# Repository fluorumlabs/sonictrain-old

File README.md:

# FluorumLabs / SonicTrain

This is the schematics and PCB repository for the second revision of SonicTrain: Hardware analog audio signal chain modules.

Version: 0.1-alpha2

Modules

Module | Revision | Status | Current Consumption (+15V / -15V) | Known issues
------ | -------- | ----------- | ------------ | ------- |
M101 Power Supply | B | Tested | | Polarity protection diode bridge is getting hot (50ºC) (#24)
M202 Stereo Input | C | Tested | 21mA / 35mA |
M303 Stereo Output | C | Tested | 31mA / 45mA |
M907 VU Meter | A | | |
M913 Dev Adapter | A | Tested | 5mA / 5mA | Blue LED is brighter then Red LED (#25)
A111 Fader | A | | |
A210 4-Band EQ | A | | |
A212 Kill EQ | A | | |
A405 Diode Distortion | A | Tested | 55mA / 60mA | Diodes should be connected to ground instead of OpAmp (#19), Output gain too low (#20)
A406 4069 Overdrive | A | | |
D104 LoFi Delay | A | Tested | |
D108 SpinSemi FX | A | Fail |  |
D709 VS1053 Synth | A | | |

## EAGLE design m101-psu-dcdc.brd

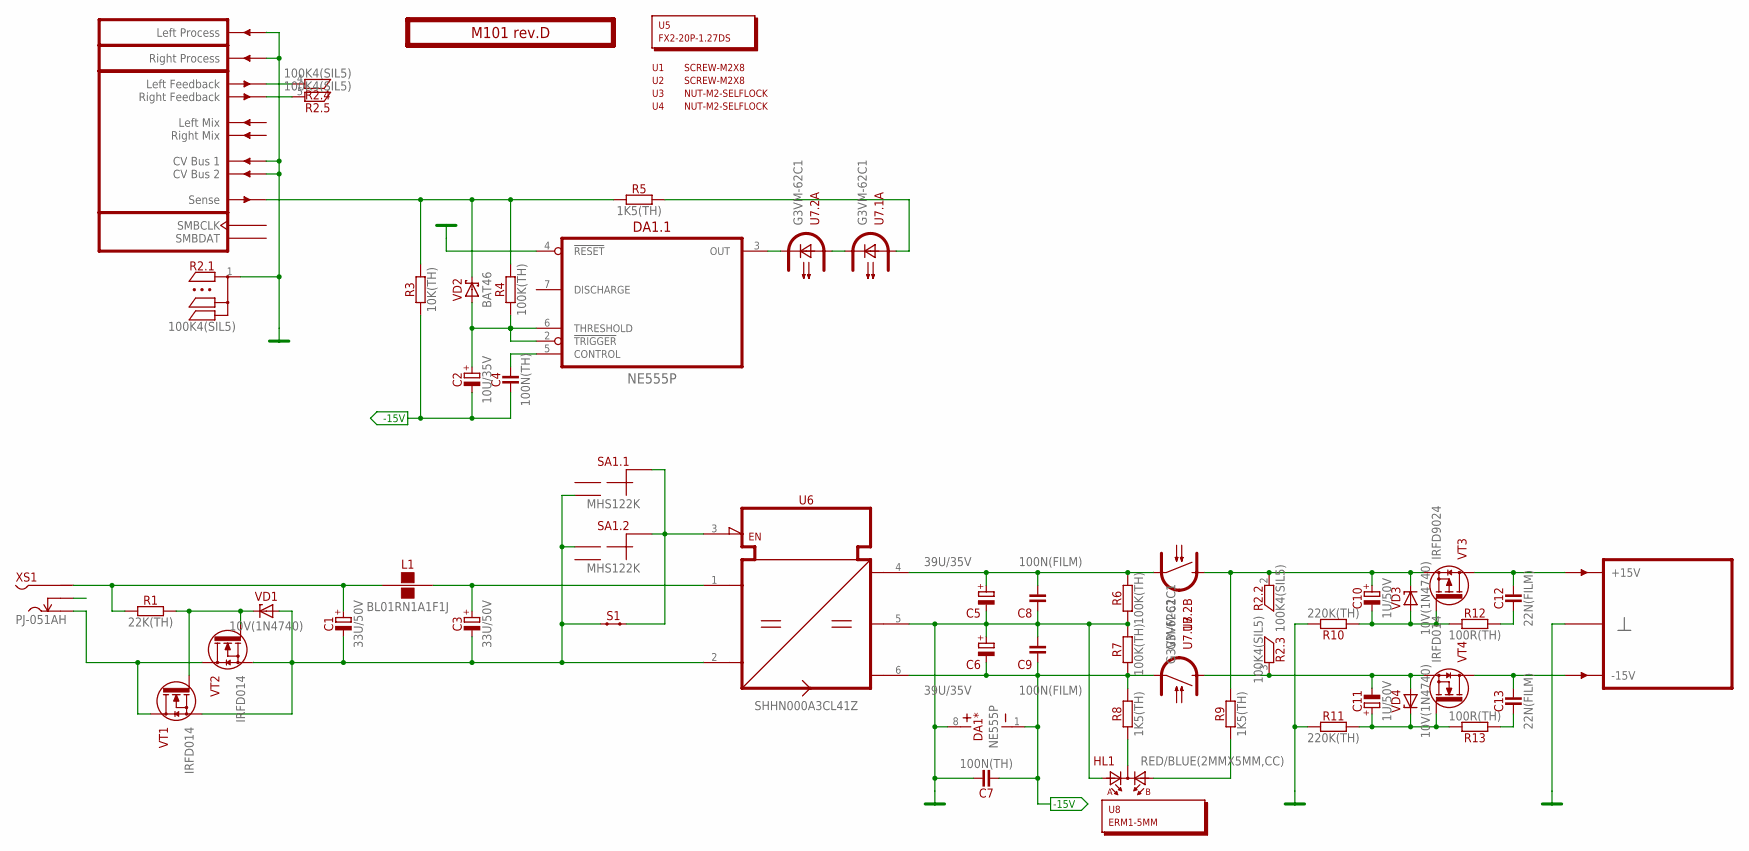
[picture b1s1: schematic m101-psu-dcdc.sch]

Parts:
C1, C3: 33U/50V; E3,5-8
C2: 10U/35V; E2-5
C4, C7: 100N(TH); C050-024X044
C5, C6: 39U/35V; E3,5-8
C8, C9: 100N(FILM); C050-025X075
C10, C11: 1U/50V; E1,5-4
C12, C13: 22N(FILM); C050-025X075
DA1: NE555P; DIP-8
HL1: RED/BLUE(2MMX5MM,CC); LED2X5-3PIN
L1: BL01RN1A1F1J; BL01RN1A
PCB1: M101 rev.D; ST2-BOARD-50-PSU
R1: 22K(TH); R-0207/10
R2: 100K4(SIL5); R-SIL5
R3: 10K(TH); R-0207/10
R4, R6, R7: 100K(TH); R-0207/10
R5, R8, R9: 1K5(TH); R-0207/10
R10, R11: 220K(TH); R-0207/10
R12, R13: 100R(TH); R-0207/10
S1: JUMPER-1POS-SOLDER; JP1-SOLDER
SA1: MHS122K; APEM-MHS122K
U1, U2: SCREW-M2X8; EMPTY
U3, U4: NUT-M2-SELFLOCK; EMPTY
U5: FX2-20P-1.27DS; EMPTY
U6: SHHN000A3CL41Z; DC/DC-C1
U7: G3VM-62C1; DIL08
U8: ERM1-5MM; EMPTY
VD1, VD3, VD4: 10V(1N4740); DO41-10
VD2: BAT46; DO35-7
VT1, VT2, VT4: IRFD014; HVMDIP-4
VT3: IRFD9024; HVMDIP-4
XS1: PJ-051AH

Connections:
-15V: C2.-, C4.1, C6.-, C7.1, C9.1, DA1.1 (V-), R3.1, R7.1, R8.2, U6.6 (V-), U7.7 (S2)
GND: C5.-, C6.+, C7.2, C8.1, C9.2, DA1.4 (!RESET), DA1.8 (V+), HL1.A1, PCB1.ACV1' (CV1'), PCB1.ACV2' (CV2'), PCB1.B4' (GND), PCB1.B5' (GND), PCB1.B6' (GND), PCB1.B7' (GND), PCB1.B8' (GND), PCB1.BOUTL' (OUTL), PCB1.BOUTR' (OUTR), R2.1, R6.1, R7.2, R10.2, R11.2, U6.5 (GND)
unnamed: R5.2, U7.1 (A)
unnamed: C1.-, C3.-, S1.1, SA1.1' (1), SA1.2, U6.2 (IN-), VD1.A, VT1.4 (S), VT2.4 (S)
unnamed: PCB1.ALFBK' (LFBK'), R2.4
unnamed: PCB1.ARFBK' (RFBK'), R2.5
unnamed: C4.2, DA1.5 (CONTROL)
unnamed: DA1.3 (OUT), U7.4 (C)
unnamed: VT1.1 (D), VT1.2 (D), VT2.1 (D), VT2.2 (D), XS1.3 (S)
unnamed: U7.2 (C), U7.3 (A)
unnamed: C2.+, DA1.2 (!TRIGGER), DA1.6 (THRESHOLD), R4.1, VD2.A
unnamed: C10.+, R2.2, R9.2, U7.6 (S1), VD3.C, VT3.4 (S)
unnamed: R1.2, VD1.C, VT1.3 (G), VT2.3 (G)
unnamed: HL1.K, R8.1
unnamed: HL1.A2, R9.1
unnamed: C5.+, C8.2, R6.2, U6.4 (V+), U7.5 (S2)
unnamed: S1.2, SA1.CMN (CM), SA1.CMN' (CM), U6.3 (EN)
unnamed: C10.-, R10.1, R12.1, VD3.A, VT3.3 (G)
unnamed: C12.2, PCB1.A+15' (P+15V), PCB1.B+15' (P+15V), VT3.1 (D), VT3.2 (D)
unnamed: C12.1, R12.2
unnamed: C1.+, L1.1, R1.1, XS1.1
unnamed: C13.1, PCB1.A-15' (P-15V), PCB1.B-15' (P-15V), VT4.1 (D), VT4.2 (D)
unnamed: C3.+, L1.2, U6.1 (IN+)
unnamed: C13.2, R13.2
unnamed: C11.+, R11.1, R13.1, VD4.C, VT4.3 (G)
unnamed: C11.-, R2.3, U7.8 (S1), VD4.A, VT4.4 (S)
SENSE: PCB1.BSENSE' (SENSE'), R3.2, R4.2, R5.1, VD2.C

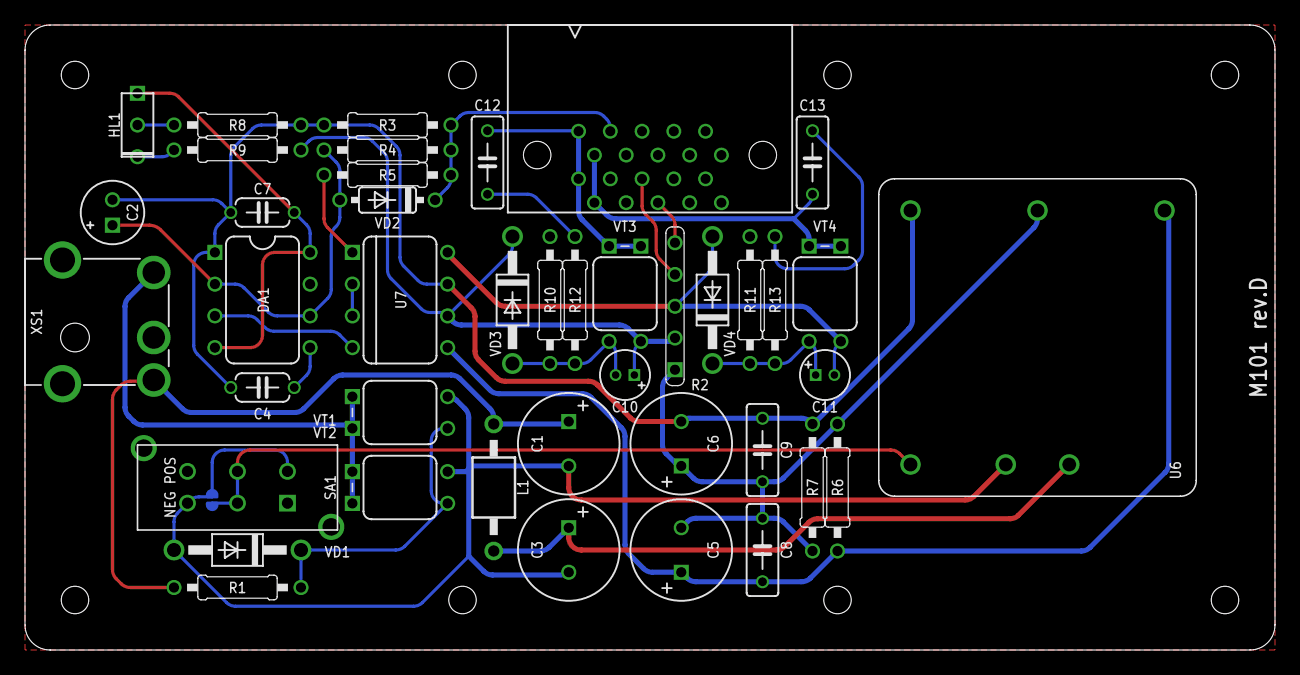
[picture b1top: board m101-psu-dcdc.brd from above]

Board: 2 copper layers, 100.0 x 50.0 mm, 49 parts (1 on the bottom side), 27 nets.

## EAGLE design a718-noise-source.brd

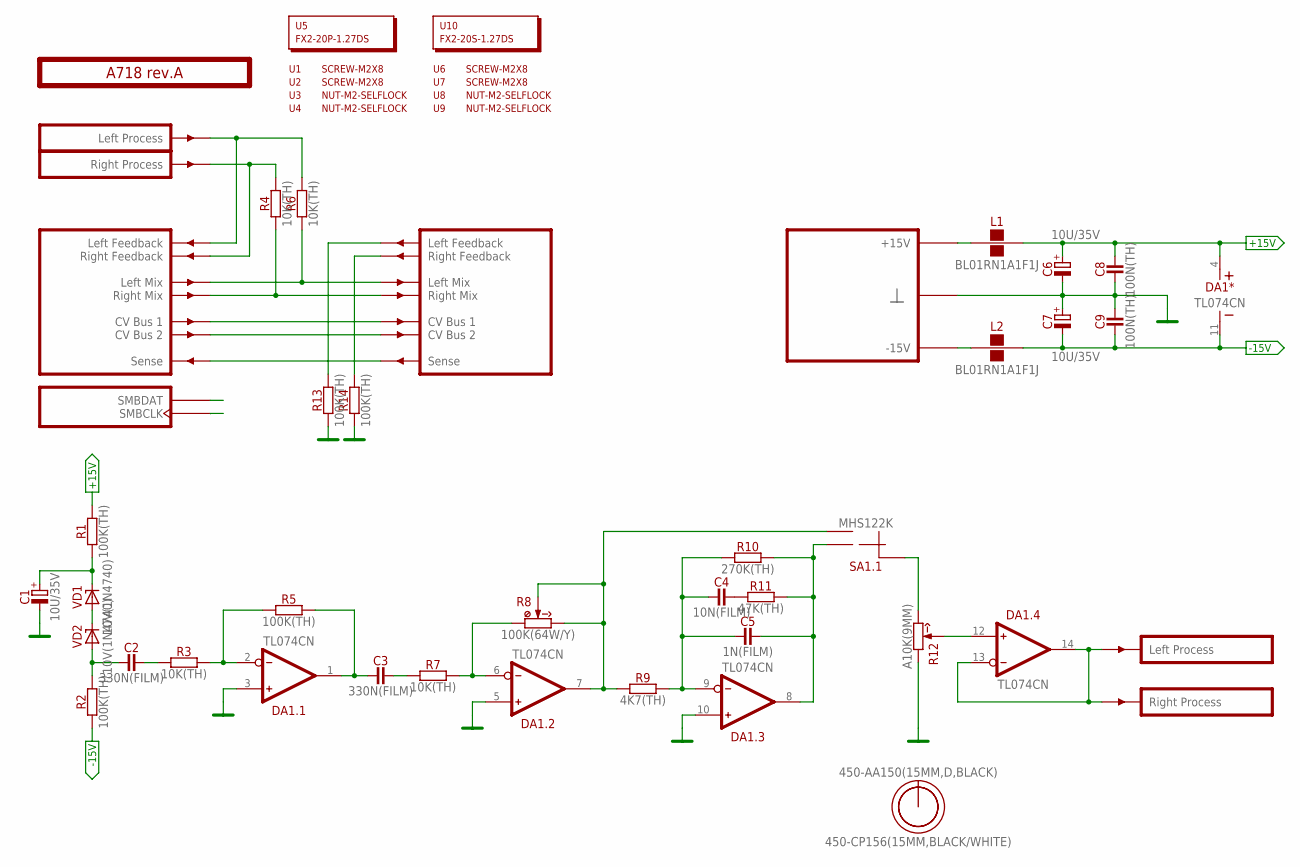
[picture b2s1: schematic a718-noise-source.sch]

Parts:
C1, C6, C7: 10U/35V; E2-5
C2, C3: 330N(FILM); C050-035X075
C4: 10N(FILM); C050-025X075
C5: 1N(FILM); C050-025X075
C8, C9: 100N(TH); C050-024X044
DA1: TL074CN; DIP-14
L1, L2: BL01RN1A1F1J; BL01RN1A
O1: 450-AA150(15MM,D,BLACK); EMPTY
O2: 450-CP156(15MM,BLACK/WHITE); EMPTY
PCB1: A718 rev.A; ST2-BOARD-50
R1, R2, R5, R13, R14: 100K(TH); R-0207/10
R3, R4, R6, R7: 10K(TH); R-0207/10
R8: 100K(64W/Y); 64W
R9: 4K7(TH); R-0207/10
R10: 270K(TH); R-0207/10
R11: 47K(TH); R-0207/10
R12: A10K(9MM); RV09-SINGLE
SA1: MHS122K; APEM-MHS122K
U1, U2, U6, U7: SCREW-M2X8; EMPTY
U3, U4, U8, U9: NUT-M2-SELFLOCK; EMPTY
U5: FX2-20P-1.27DS; EMPTY
U10: FX2-20S-1.27DS; EMPTY
VD1, VD2: 10V(1N4740); DO41-10

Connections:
+15V: C6.+, C8.2, DA1.4 (V+), L1.2, R1.2
-15V: C7.-, C9.1, DA1.11 (V-), L2.2, R2.1
GND: C1.-, C6.-, C7.+, C8.1, C9.2, DA1.3 (IN+), DA1.5 (IN+), DA1.10 (IN+), PCB1.B4 (GND), PCB1.B4' (GND), PCB1.B5 (GND), PCB1.B5' (GND), PCB1.B6 (GND), PCB1.B6' (GND), PCB1.B7 (GND), PCB1.B7' (GND), PCB1.B8 (GND), PCB1.B8' (GND), R12.1 (CCW), R13.1, R14.1
LMIX: PCB1.ALMIX (LMIX), PCB1.ALMIX' (LMIX'), R6.1
unnamed: L1.1, PCB1.A+15 (P+15V), PCB1.A+15' (P+15V), PCB1.B+15 (P+15V), PCB1.B+15' (P+15V)
unnamed: C1.+, R1.1, VD1.C
unnamed: PCB1.ARFBK' (RFBK'), R14.2
unnamed: VD1.A, VD2.C
unnamed: L2.1, PCB1.A-15 (P-15V), PCB1.A-15' (P-15V), PCB1.B-15 (P-15V), PCB1.B-15' (P-15V)
unnamed: PCB1.ALFBK' (LFBK'), R13.2
unnamed: C2.1, R2.2, VD2.A
unnamed: C4.1, C5.1, DA1.9 (IN-), R9.2, R10.1
unnamed: C2.2, R3.1
unnamed: DA1.2 (IN-), R3.2, R5.1
unnamed: C3.1, DA1.1 (OUT), R5.2
unnamed: C3.2, R7.1
unnamed: DA1.6 (IN-), R7.2, R8.1 (CCW)
unnamed: DA1.7 (OUT), R8.3 (CW), R8.S (W), R8.S@1 (W), R9.1, SA1.2
unnamed: C4.2, R11.1
unnamed: PCB1.BSENSE (SENSE), PCB1.BSENSE' (SENSE')
unnamed: PCB1.ARFBK (RFBK), PCB1.BINR (INR), R4.2
unnamed: PCB1.ALFBK (LFBK), PCB1.BINL (INL), R6.2
unnamed: C5.2, DA1.8 (OUT), R10.2, R11.2, SA1.1
unnamed: R12.3 (CW), SA1.CMN (CM)
unnamed: DA1.12 (IN+), R12.2 (W)
unnamed: DA1.13 (IN-), DA1.14 (OUT), PCB1.BOUTL' (OUTL), PCB1.BOUTR' (OUTR)
unnamed: PCB1.ASMBDAT (SMBDAT), PCB1.ASMBDAT' (SMBDAT)
unnamed: PCB1.ACV1 (CV1), PCB1.ACV1' (CV1')
unnamed: PCB1.ACV2 (CV2), PCB1.ACV2' (CV2')
unnamed: PCB1.ASMBCLK (SMBCLK), PCB1.ASMBCLK' (SMBCLK)
RMIX: PCB1.ARMIX (RMIX), PCB1.ARMIX' (RMIX'), R4.1

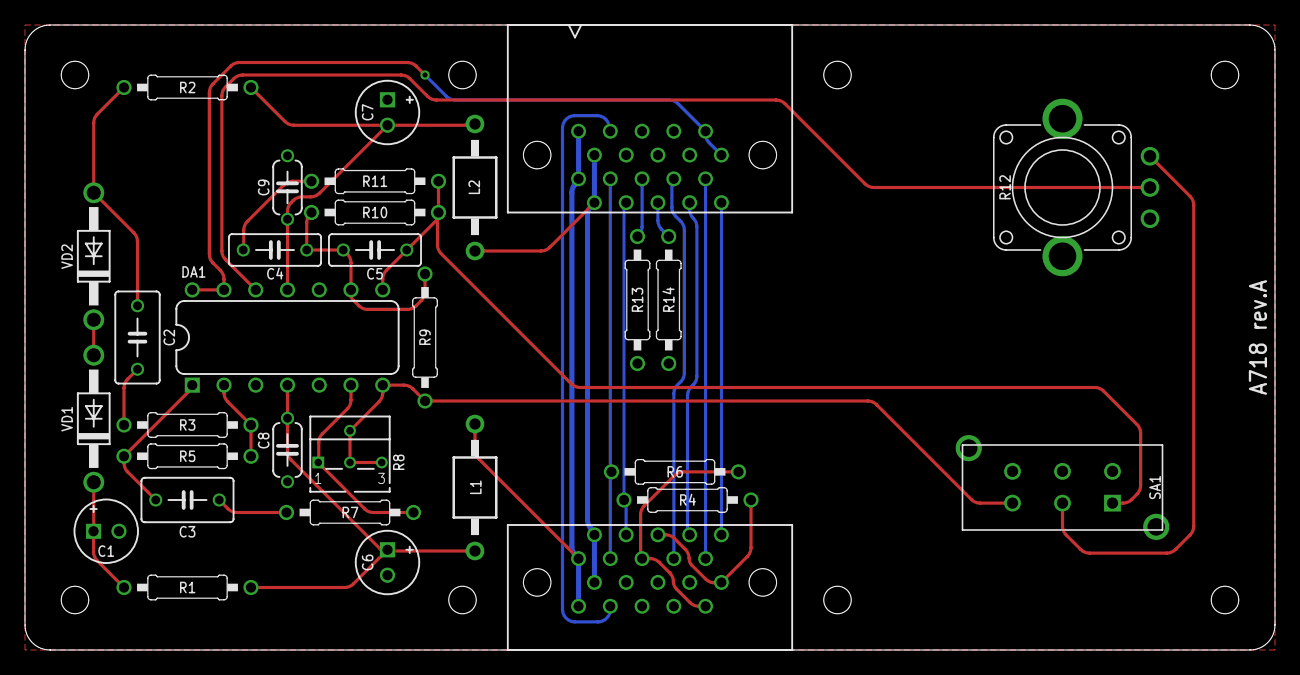
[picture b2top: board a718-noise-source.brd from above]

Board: 2 copper layers, 100.0 x 50.0 mm, 42 parts (0 on the bottom side), 31 nets.

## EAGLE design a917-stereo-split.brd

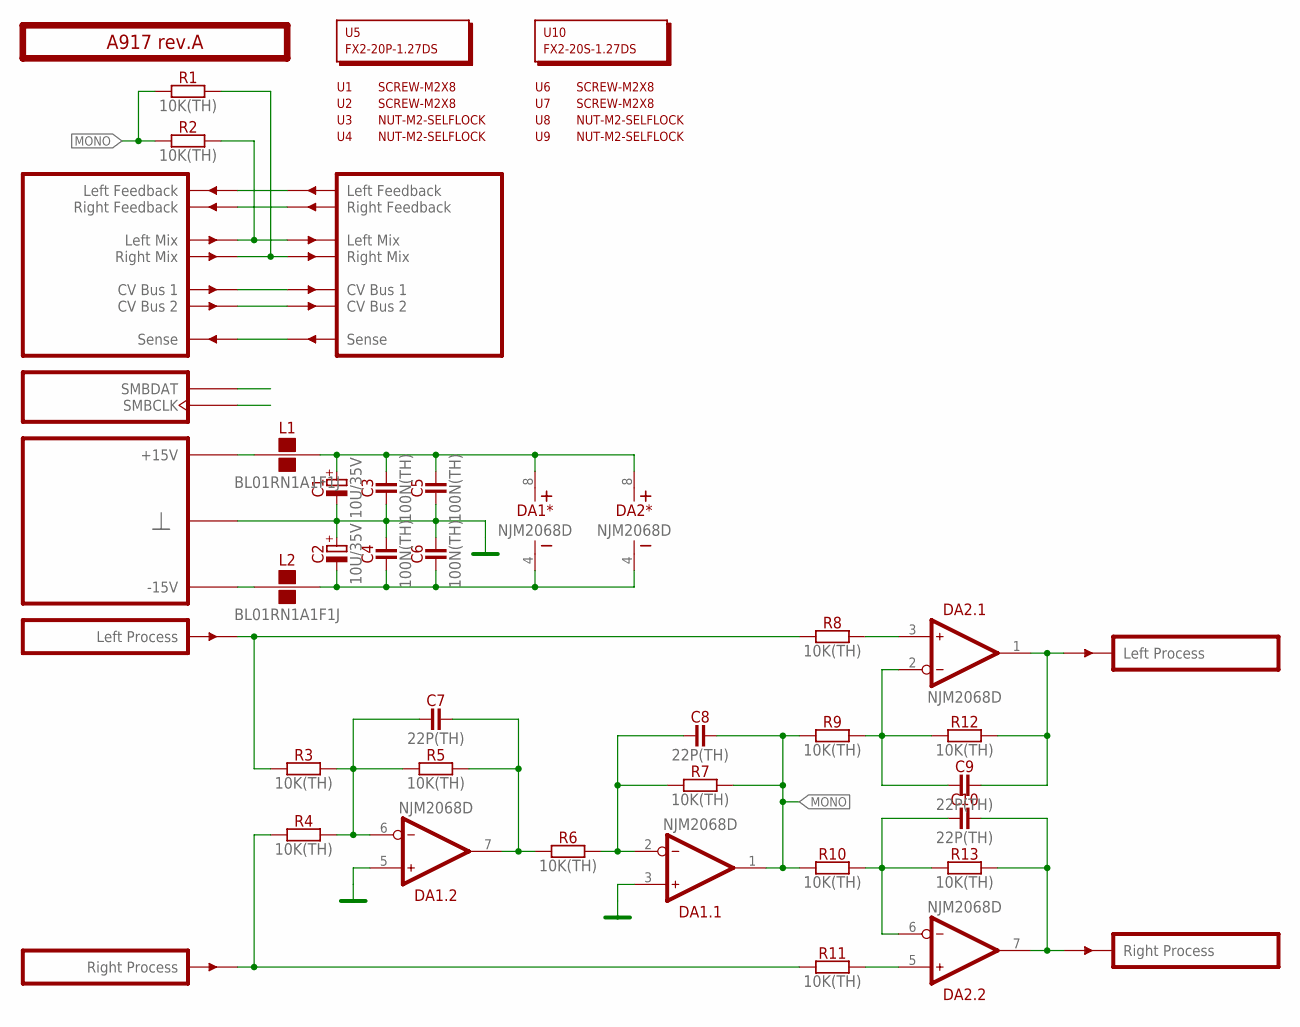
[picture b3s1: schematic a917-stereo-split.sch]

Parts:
C1, C2: 10U/35V; E2-5
C3, C4, C5, C6: 100N(TH); C050-024X044
C7, C8, C9, C10: 22P(TH); C050-024X044
DA1, DA2: NJM2068D; DIP-8
L1, L2: BL01RN1A1F1J; BL01RN1A
PCB1: A917 rev.A; ST2-BOARD-26
R1, R2, R3, R4, R5, R6, R7, R8, R9, R10, R11, R12, R13: 10K(TH); R-0207/10
U1, U2, U6, U7: SCREW-M2X8; EMPTY
U3, U4, U8, U9: NUT-M2-SELFLOCK; EMPTY
U5: FX2-20P-1.27DS; EMPTY
U10: FX2-20S-1.27DS; EMPTY

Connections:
GND: C1.-, C2.+, C3.1, C4.2, C5.1, C6.2, DA1.3 (IN+), DA1.5 (IN+), PCB1.B4 (GND), PCB1.B4' (GND), PCB1.B5 (GND), PCB1.B5' (GND), PCB1.B6 (GND), PCB1.B6' (GND), PCB1.B7 (GND), PCB1.B7' (GND), PCB1.B8 (GND), PCB1.B8' (GND)
MONO: C8.2, DA1.1 (OUT), R1.1, R2.1, R7.2, R9.1, R10.1
unnamed: PCB1.ALFBK (LFBK), PCB1.ALFBK' (LFBK')
unnamed: PCB1.ARFBK (RFBK), PCB1.ARFBK' (RFBK')
unnamed: PCB1.ALMIX (LMIX), PCB1.ALMIX' (LMIX'), R2.2
unnamed: PCB1.ARMIX (RMIX), PCB1.ARMIX' (RMIX'), R1.2
unnamed: PCB1.ACV1 (CV1), PCB1.ACV1' (CV1')
unnamed: PCB1.ACV2 (CV2), PCB1.ACV2' (CV2')
unnamed: PCB1.BSENSE (SENSE), PCB1.BSENSE' (SENSE')
unnamed: PCB1.ASMBDAT (SMBDAT), PCB1.ASMBDAT' (SMBDAT)
unnamed: PCB1.ASMBCLK (SMBCLK), PCB1.ASMBCLK' (SMBCLK)
unnamed: C7.1, DA1.6 (IN-), R3.2, R4.2, R5.1
unnamed: C7.2, DA1.7 (OUT), R5.2, R6.1
unnamed: C8.1, DA1.2 (IN-), R6.2, R7.1
unnamed: DA2.3 (IN+), R8.2
unnamed: C9.1, DA2.2 (IN-), R9.2, R12.1
unnamed: C9.2, DA2.1 (OUT), PCB1.BOUTL' (OUTL), R12.2
unnamed: DA2.5 (IN+), R11.2
unnamed: C10.1, DA2.6 (IN-), R10.2, R13.1
unnamed: C10.2, DA2.7 (OUT), PCB1.BOUTR' (OUTR), R13.2
unnamed: PCB1.BINL (INL), R3.1, R8.1
unnamed: PCB1.BINR (INR), R4.1, R11.1
unnamed: L1.1, PCB1.A+15 (P+15V), PCB1.A+15' (P+15V), PCB1.B+15 (P+15V), PCB1.B+15' (P+15V)
unnamed: C1.+, C3.2, C5.2, DA1.8 (V+), DA2.8 (V+), L1.2
unnamed: L2.1, PCB1.A-15 (P-15V), PCB1.A-15' (P-15V), PCB1.B-15 (P-15V), PCB1.B-15' (P-15V)
unnamed: C2.-, C4.1, C6.1, DA1.4 (V-), DA2.4 (V-), L2.2

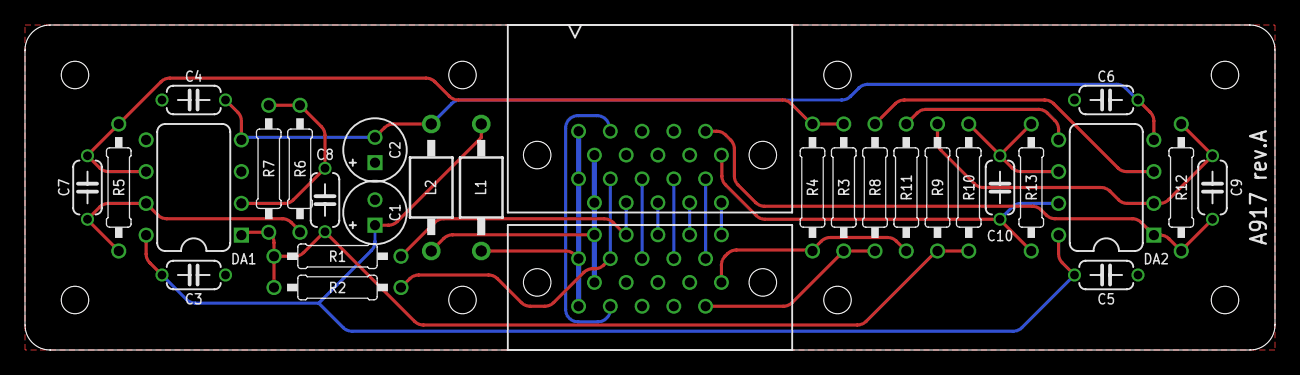
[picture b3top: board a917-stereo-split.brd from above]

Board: 2 copper layers, 100.0 x 26.0 mm, 38 parts (0 on the bottom side), 26 nets.

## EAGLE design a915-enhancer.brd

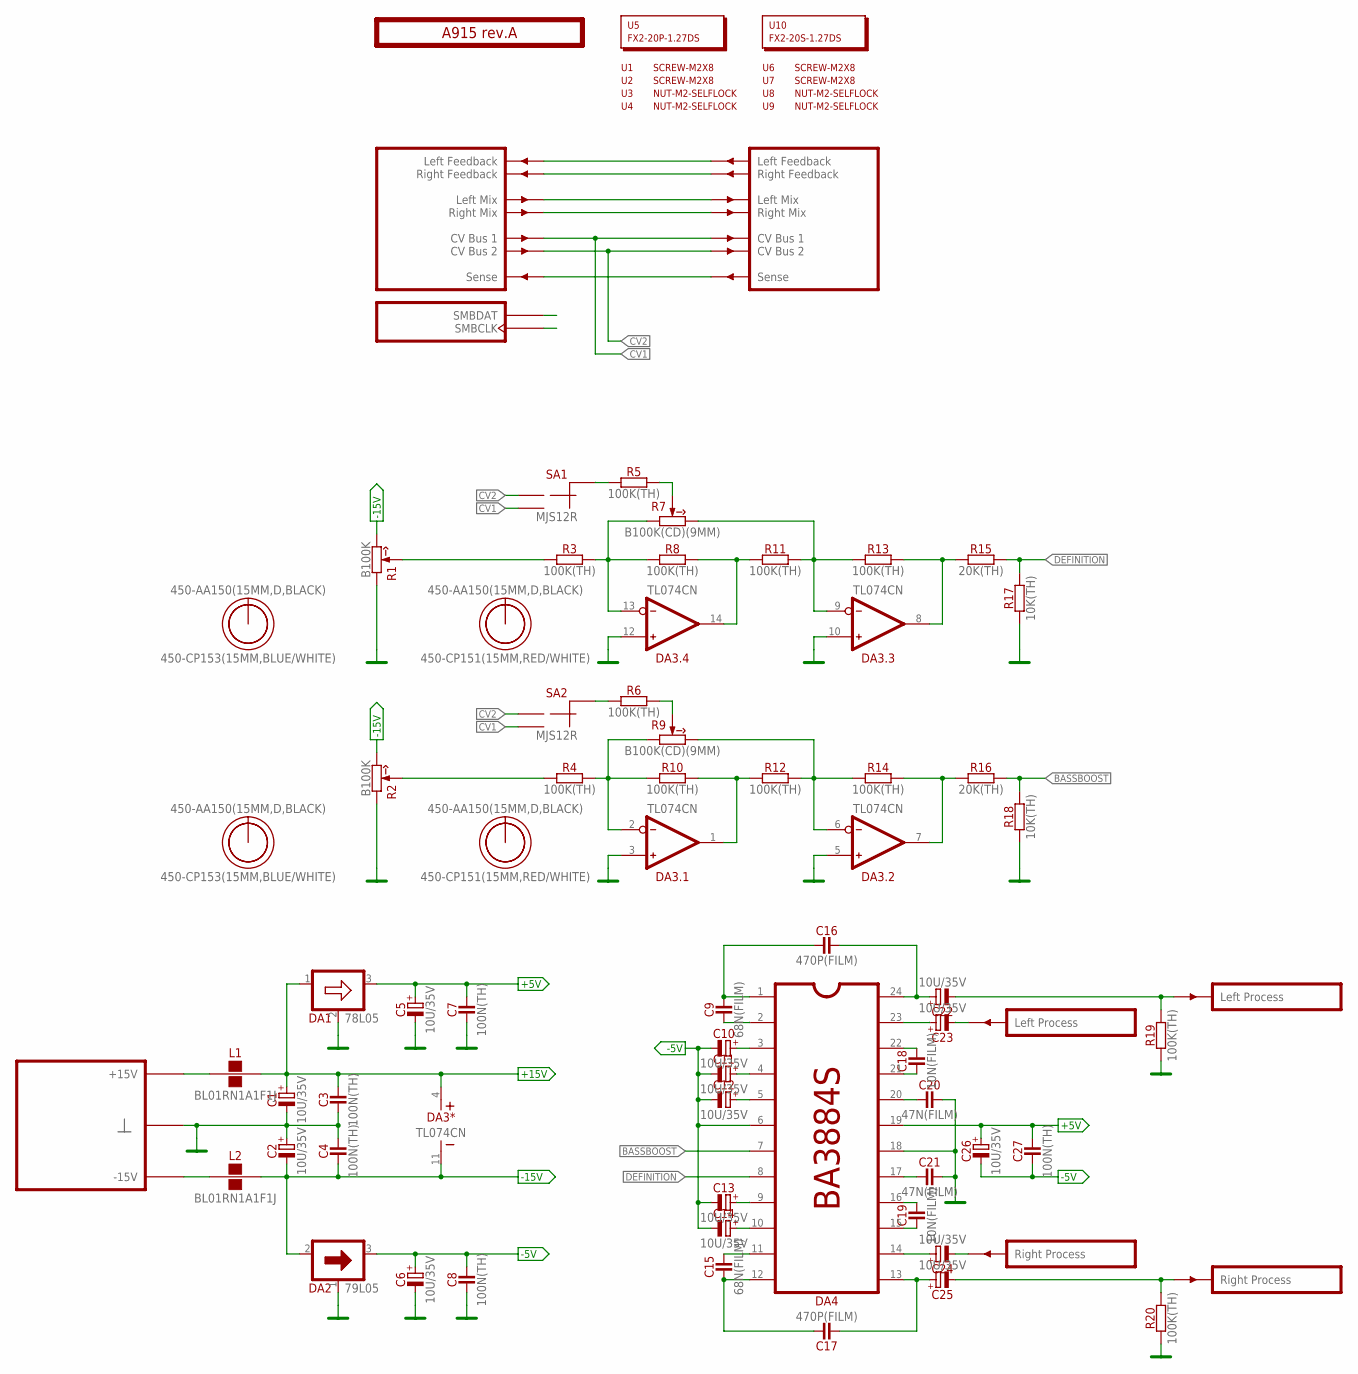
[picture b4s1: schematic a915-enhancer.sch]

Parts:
C1, C2, C5, C6, C10, C11, C12, C13, C14, C22, C23, C24, C25, C26: 10U/35V; E2-5
C3, C4, C7, C8, C27: 100N(TH); C050-024X044
C9, C15: 68N(FILM); C050-025X075
C16, C17: 470P(FILM); C050-055X075
C18, C19: 10N(FILM); C050-025X075
C20, C21: 47N(FILM); C050-025X075
DA1: 78L05; TO92
DA2: 79L05; TO92
DA3: TL074CN; DIP-14
DA4: BA3884S; SDIP-24
L1, L2: BL01RN1A1F1J; BL01RN1A
O1, O3, O5, O7: 450-AA150(15MM,D,BLACK); EMPTY
O2, O4: 450-CP153(15MM,BLUE/WHITE); EMPTY
O6, O8: 450-CP151(15MM,RED/WHITE); EMPTY
PCB1: A915 rev.A; ST2-BOARD-50
R1, R2: B100K; RV11-SINGLE
R3, R4, R5, R6, R8, R10, R11, R12, R13, R14, R19, R20: 100K(TH); R-0207/10
R7, R9: B100K(CD)(9MM); RV09-SINGLE
R15, R16: 20K(TH); R-0207/10
R17, R18: 10K(TH); R-0207/10
SA1, SA2: MJS12R; APEM-MJS12R
U1, U2, U6, U7: SCREW-M2X8; EMPTY
U3, U4, U8, U9: NUT-M2-SELFLOCK; EMPTY
U5: FX2-20P-1.27DS; EMPTY
U10: FX2-20S-1.27DS; EMPTY

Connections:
+5V: C5.+, C7.2, C26.+, C27.2, DA1.3 (OUT), DA4.19
+15V: C1.+, C3.2, DA1.1 (IN), DA3.4 (V+), L1.2
-5V: C6.+, C8.2, C10.-, C11.-, C12.-, C13.-, C14.-, C26.-, C27.1, DA2.3 (OUT), DA4.6
-15V: C2.-, C4.1, DA2.2 (IN), DA3.11 (V-), L2.2, R1.3 (CW), R2.3 (CW)
BASSBOOST: DA4.7, R16.2, R18.2
CV1: PCB1.ACV1 (CV1), PCB1.ACV1' (CV1'), SA1.NO (2), SA2.NO (2)
CV2: PCB1.ACV2 (CV2), PCB1.ACV2' (CV2'), SA1.NC (1), SA2.NC (1)
DEFINITION: DA4.8, R15.2, R17.2
GND: C1.-, C2.+, C3.1, C4.2, C5.-, C6.-, C7.1, C8.1, C20.2, C21.2, DA1.2 (GND), DA2.1 (GND), DA3.3 (IN+), DA3.5 (IN+), DA3.10 (IN+), DA3.12 (IN+), DA4.18, PCB1.B4 (GND), PCB1.B4' (GND), PCB1.B5 (GND), PCB1.B5' (GND), PCB1.B6 (GND), PCB1.B6' (GND), PCB1.B7 (GND), PCB1.B7' (GND), PCB1.B8 (GND), PCB1.B8' (GND), R1.1 (CCW), R2.1 (CCW), R17.1, R18.1, R19.1, R20.1
LMIX: PCB1.ALMIX (LMIX), PCB1.ALMIX' (LMIX')
unnamed: L1.1, PCB1.A+15 (P+15V), PCB1.A+15' (P+15V), PCB1.B+15 (P+15V), PCB1.B+15' (P+15V)
unnamed: PCB1.ALFBK (LFBK), PCB1.ALFBK' (LFBK')
unnamed: R5.2, R7.2 (W)
unnamed: PCB1.ARFBK (RFBK), PCB1.ARFBK' (RFBK')
unnamed: DA3.13 (IN-), R3.2, R7.1 (CCW), R8.1
unnamed: DA3.14 (OUT), R8.2, R11.1
unnamed: DA3.9 (IN-), R7.3 (CW), R11.2, R13.1
unnamed: DA3.8 (OUT), R13.2, R15.1
unnamed: R5.1, SA1.C (CM)
unnamed: R1.2 (W), R3.1
unnamed: C24.+, DA4.14
unnamed: C9.1, DA4.2
unnamed: C9.2, C16.1, DA4.1
unnamed: C15.2, DA4.11
unnamed: C23.+, DA4.23
unnamed: PCB1.BSENSE (SENSE), PCB1.BSENSE' (SENSE')
unnamed: C15.1, C17.2, DA4.12
unnamed: C14.+, DA4.10
unnamed: C13.+, DA4.9
unnamed: C12.+, DA4.5
unnamed: C11.+, DA4.4
unnamed: C10.+, DA4.3
unnamed: C18.1, DA4.21
unnamed: C18.2, DA4.22
unnamed: L2.1, PCB1.A-15 (P-15V), PCB1.A-15' (P-15V), PCB1.B-15 (P-15V), PCB1.B-15' (P-15V)
unnamed: C19.1, DA4.15
unnamed: C19.2, DA4.16
unnamed: C21.1, DA4.17
unnamed: C20.1, DA4.20
unnamed: R6.2, R9.2 (W)
unnamed: DA3.2 (IN-), R4.2, R9.1 (CCW), R10.1
unnamed: C16.2, C22.+, DA4.24
unnamed: C17.1, C25.+, DA4.13
unnamed: DA3.1 (OUT), R10.2, R12.1
unnamed: DA3.6 (IN-), R9.3 (CW), R12.2, R14.1
unnamed: DA3.7 (OUT), R14.2, R16.1
unnamed: R6.1, SA2.C (CM)
unnamed: PCB1.ASMBDAT (SMBDAT), PCB1.ASMBDAT' (SMBDAT)
unnamed: R2.2 (W), R4.1
unnamed: C23.-, PCB1.BINL (INL)
unnamed: C22.-, PCB1.BOUTL' (OUTL), R19.2
unnamed: C24.-, PCB1.BINR (INR)
unnamed: PCB1.ASMBCLK (SMBCLK), PCB1.ASMBCLK' (SMBCLK)
unnamed: C25.-, PCB1.BOUTR' (OUTR), R20.2
RMIX: PCB1.ARMIX (RMIX), PCB1.ARMIX' (RMIX')

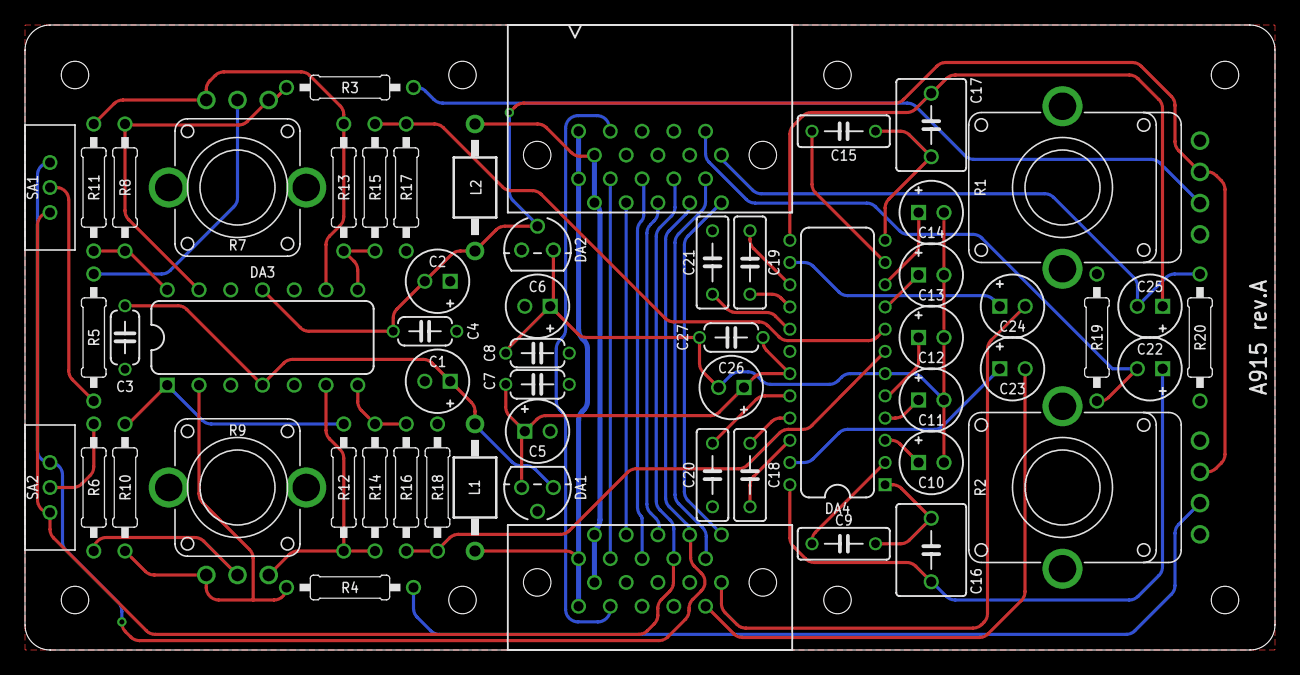
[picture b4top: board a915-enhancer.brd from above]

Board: 2 copper layers, 100.0 x 50.0 mm, 74 parts (0 on the bottom side), 55 nets.

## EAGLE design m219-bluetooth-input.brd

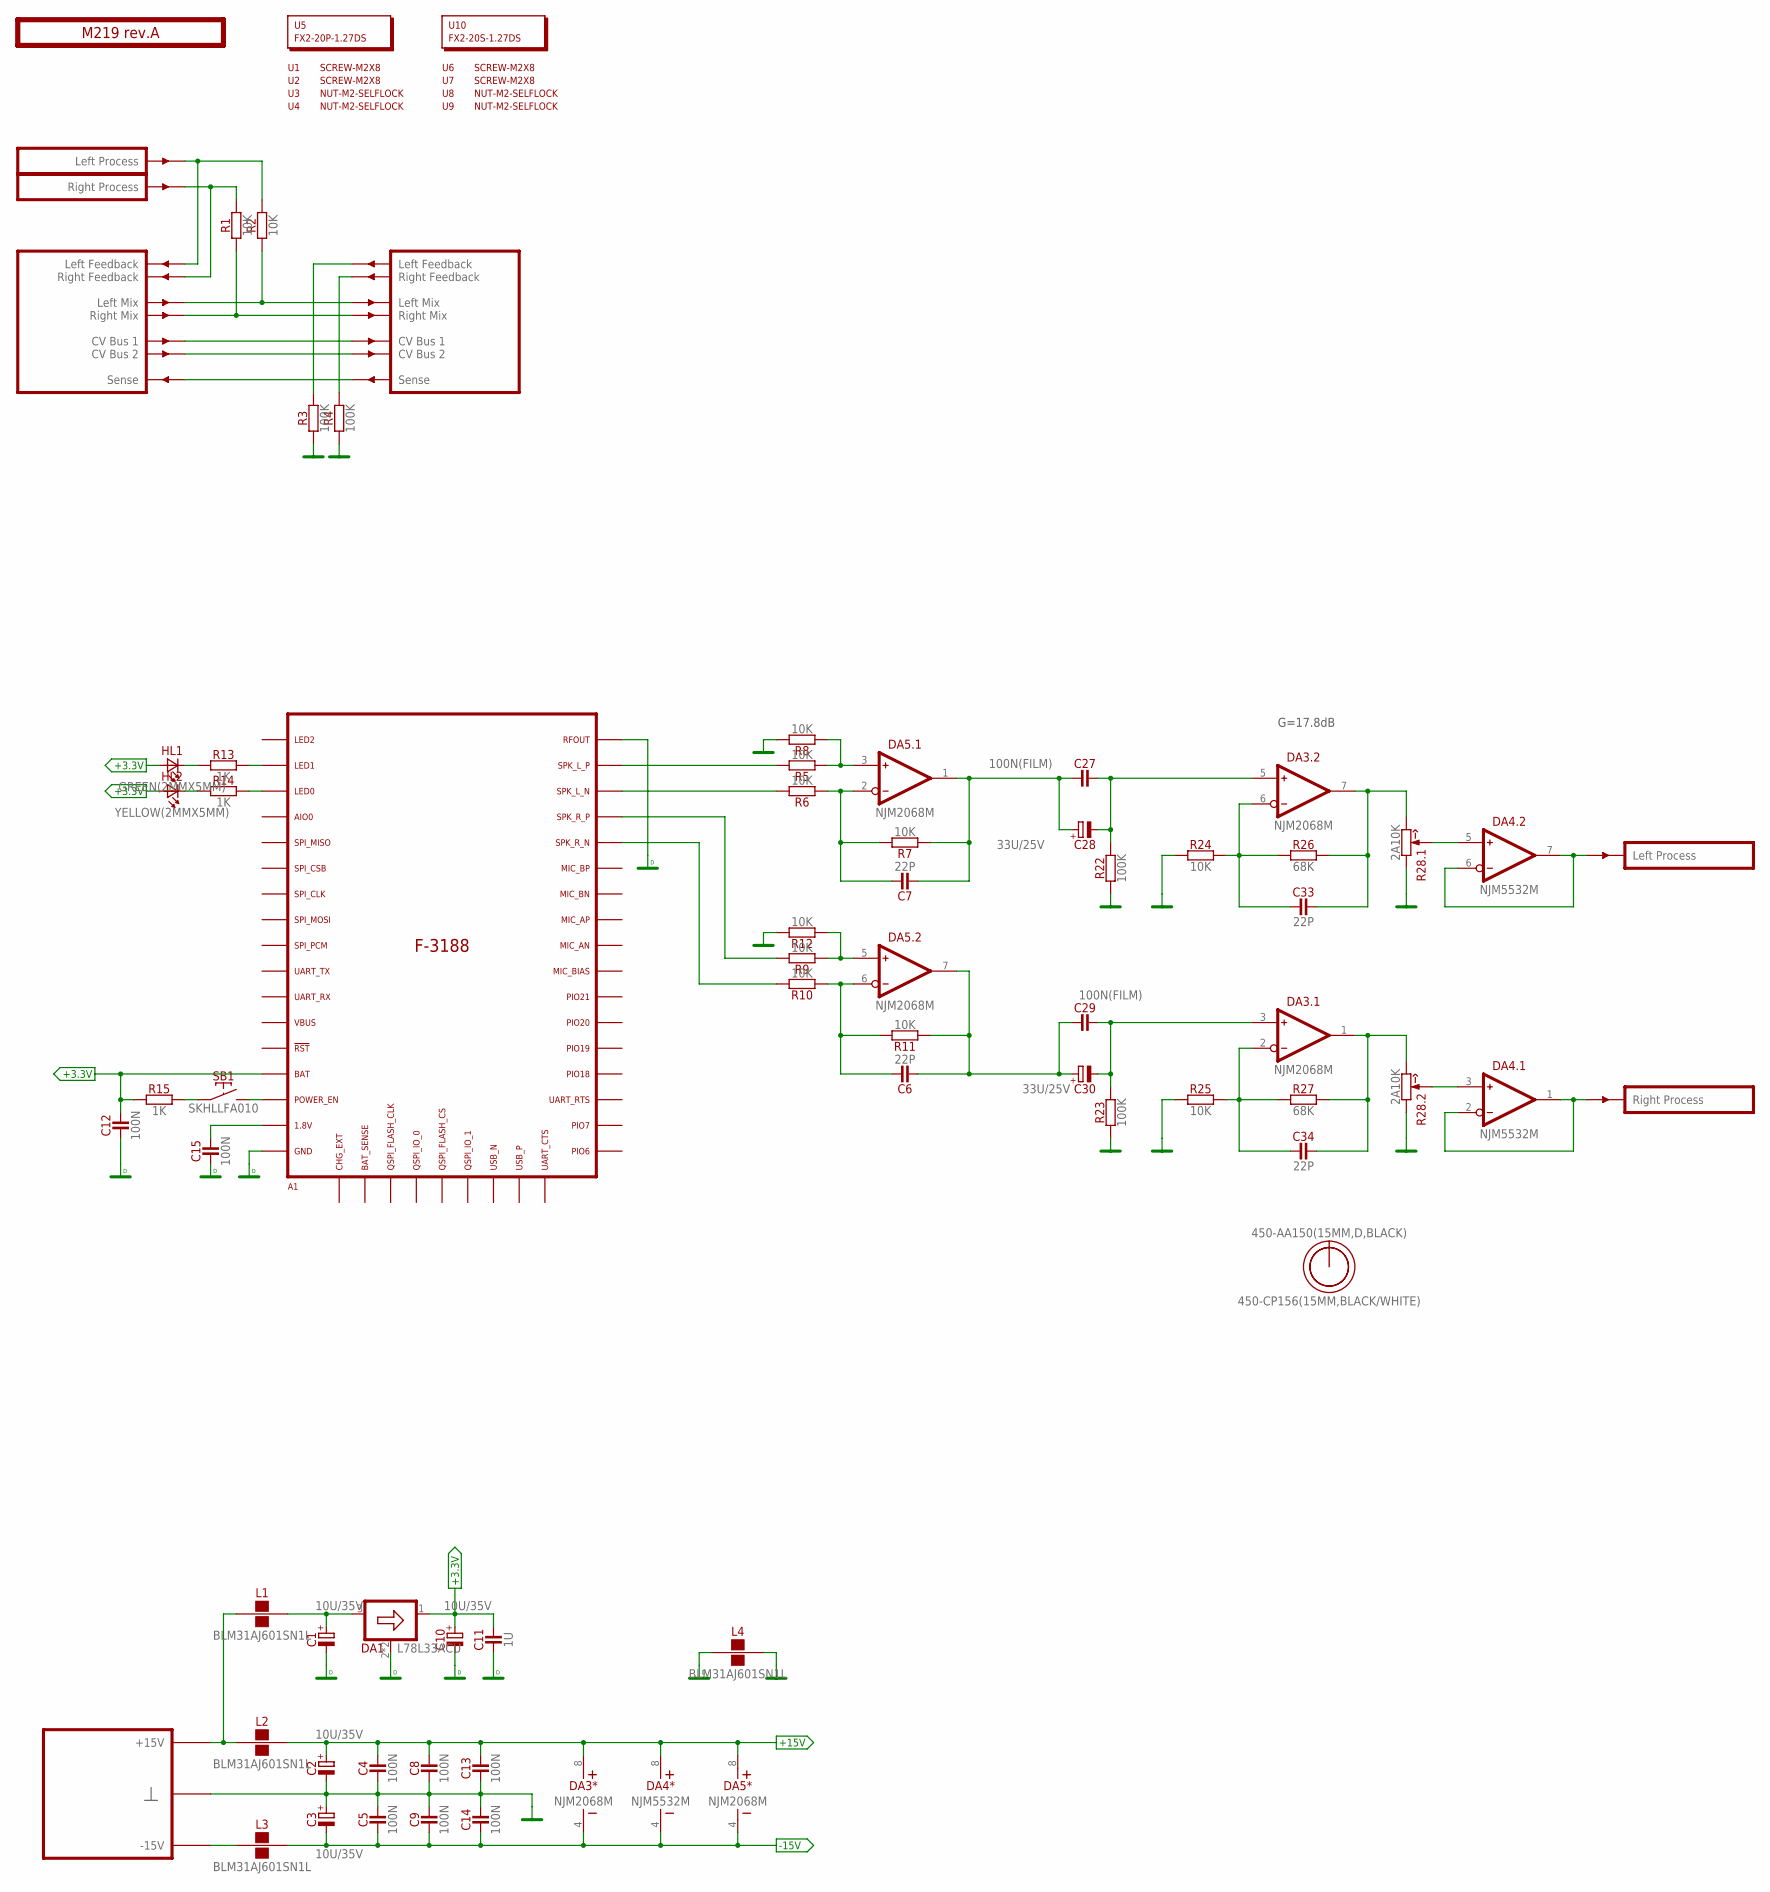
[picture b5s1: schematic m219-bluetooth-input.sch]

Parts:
A1: F3188
C1, C2, C3, C10: 10U/35V; E2-5
C4, C5, C8, C9, C12, C13, C14, C15: 100N; C-0805
C6, C7, C33, C34: 22P; C-0805
C11: 1U; C-0805
C27, C29: 100N(FILM); C050-025X075
C28, C30: 33U/25V; E2,5-7
DA1: L78L33ACU; SOT89
DA3, DA5: NJM2068M; SO-8
DA4: NJM5532M; SO-8
HL1: GREEN(2MMX5MM); LED2X5
HL2: YELLOW(2MMX5MM); LED2X5
L1, L2, L3, L4: BLM31AJ601SN1L; 1206
O1: 450-AA150(15MM,D,BLACK); EMPTY
O2: 450-CP156(15MM,BLACK/WHITE); EMPTY
PCB1: M219 rev.A; ST2-BOARD-50
R1, R2, R5, R6, R7, R8, R9, R10, R11, R12, R24, R25: 10K; R-0805
R3, R4, R22, R23: 100K; R-0805
R13, R14, R15: 1K; R-0805
R26, R27: 68K; R-0805
R28: 2A10K; RV11-DUAL
SB1: SKHLLFA010
U1, U2, U6, U7: SCREW-M2X8; EMPTY
U3, U4, U8, U9: NUT-M2-SELFLOCK; EMPTY
U5: FX2-20P-1.27DS; EMPTY
U10: FX2-20S-1.27DS; EMPTY

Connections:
+3.3V: A1.P$14 (BAT), C10.+, C11.2, C12.2, DA1.1 (OUT), HL1.A, HL2.A, R15.1
+15V: C2.+, C4.2, C8.2, C13.2, DA3.8 (V+), DA4.8 (V+), DA5.8 (V+), L2.2
-15V: C3.-, C5.1, C9.1, C14.1, DA3.4 (V-), DA4.4 (V-), DA5.4 (V-), L3.2
DGND: A1.P$17 (GND), A1.P$43 (RFOUT), C1.-, C10.-, C11.1, C12.1, C15.1, DA1.2 (GND), DA1.2@1 (GND), L4.1
GND: C2.-, C3.+, C4.1, C5.2, C8.1, C9.2, C13.1, C14.2, L4.2, PCB1.B4 (GND), PCB1.B4' (GND), PCB1.B5 (GND), PCB1.B5' (GND), PCB1.B6 (GND), PCB1.B6' (GND), PCB1.B7 (GND), PCB1.B7' (GND), PCB1.B8 (GND), PCB1.B8' (GND), R3.1, R4.1, R8.1, R12.1, R22.1, R23.1, R24.1, R25.1, R28.1 (CCW), R28.1' (CCW)
LMIX: PCB1.ALMIX (LMIX), PCB1.ALMIX' (LMIX'), R2.1
unnamed: L1.1, L2.1, PCB1.A+15 (P+15V), PCB1.A+15' (P+15V), PCB1.B+15 (P+15V), PCB1.B+15' (P+15V)
unnamed: PCB1.ARFBK' (RFBK'), R4.2
unnamed: DA5.3 (IN+), R5.2, R8.2
unnamed: PCB1.ALFBK' (LFBK'), R3.2
unnamed: L3.1, PCB1.A-15 (P-15V), PCB1.A-15' (P-15V), PCB1.B-15 (P-15V), PCB1.B-15' (P-15V)
unnamed: A1.P$42 (SPK_L_P1), R5.1
unnamed: C7.2, C27.1, C28.+, DA5.1 (OUT), R7.2
unnamed: A1.P$41 (SPK_L_N1), R6.1
unnamed: C29.2, C30.-, DA3.3 (IN+), R23.2
unnamed: C27.2, C28.-, DA3.5 (IN+), R22.2
unnamed: C34.2, DA3.1 (OUT), R27.2, R28.3' (CW)
unnamed: C33.2, DA3.7 (OUT), R26.2, R28.3 (CW)
unnamed: C33.1, DA3.6 (IN-), R24.2, R26.1
unnamed: C34.1, DA3.2 (IN-), R25.2, R27.1
unnamed: C7.1, DA5.2 (IN-), R6.2, R7.1
unnamed: PCB1.BSENSE (SENSE), PCB1.BSENSE' (SENSE')
unnamed: DA4.6 (IN-), DA4.7 (OUT), PCB1.BOUTL' (OUTL)
unnamed: HL1.K (C), R13.1
unnamed: A1.P$40 (SPK_R_P1), R9.1
unnamed: DA4.1 (OUT), DA4.2 (IN-), PCB1.BOUTR' (OUTR)
unnamed: A1.P$39 (SPK_R_N1), R10.1
unnamed: DA4.5 (IN+), R28.2 (W)
unnamed: C6.1, DA5.6 (IN-), R10.2, R11.1
unnamed: DA4.3 (IN+), R28.2' (W)
unnamed: DA5.5 (IN+), R9.2, R12.2
unnamed: HL2.K (C), R14.1
unnamed: C1.+, DA1.3 (IN), L1.2
unnamed: A1.P$2 (LED1), R13.2
unnamed: A1.P$3 (LED0), R14.2
unnamed: A1.P$16 (VBUS_1.8V), C15.2
unnamed: R15.2, SB1.1
unnamed: A1.P$15 (POWER_EN), SB1.2
unnamed: C6.2, C29.1, C30.+, DA5.7 (OUT), R11.2
unnamed: PCB1.ARFBK (RFBK), PCB1.BINR (INR), R1.2
unnamed: PCB1.ALFBK (LFBK), PCB1.BINL (INL), R2.2
unnamed: PCB1.ACV1 (CV1), PCB1.ACV1' (CV1')
unnamed: PCB1.ACV2 (CV2), PCB1.ACV2' (CV2')
RMIX: PCB1.ARMIX (RMIX), PCB1.ARMIX' (RMIX'), R1.1
VBUS: A1.P$12 (VBUS)

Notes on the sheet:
G=17.8dB

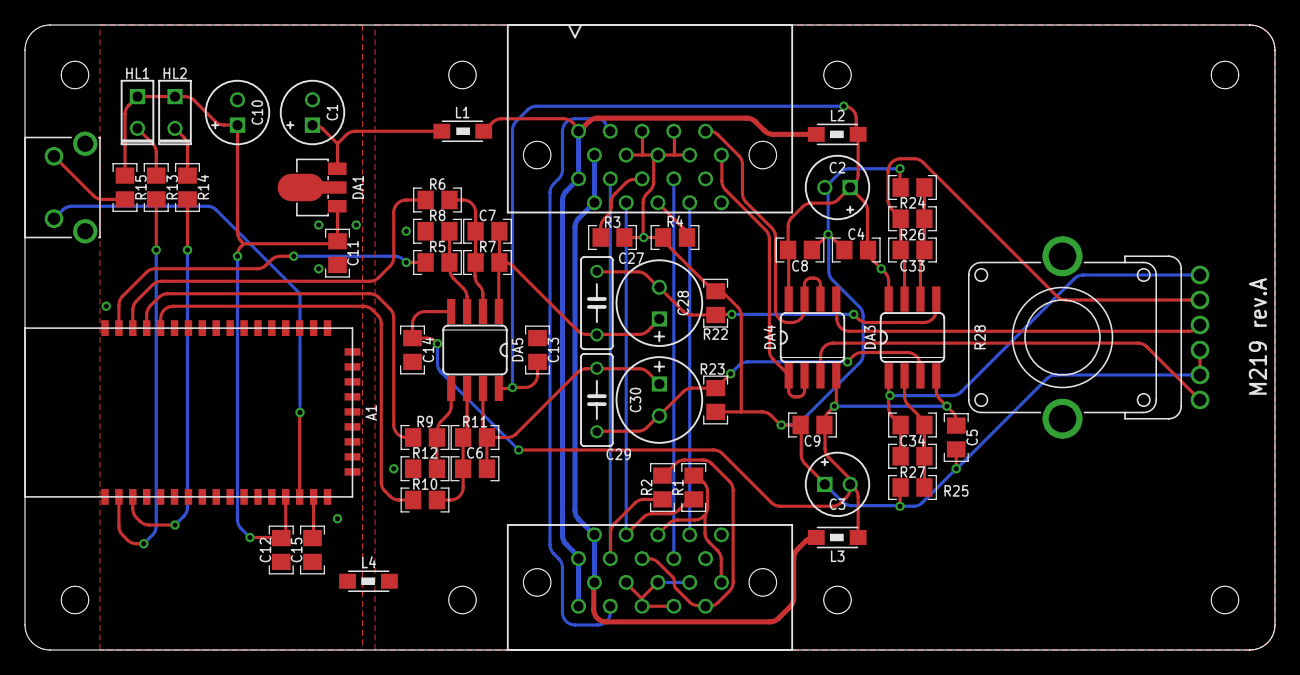
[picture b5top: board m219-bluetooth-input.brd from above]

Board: 2 copper layers, 100.0 x 50.0 mm, 68 parts (0 on the bottom side), 44 nets.
